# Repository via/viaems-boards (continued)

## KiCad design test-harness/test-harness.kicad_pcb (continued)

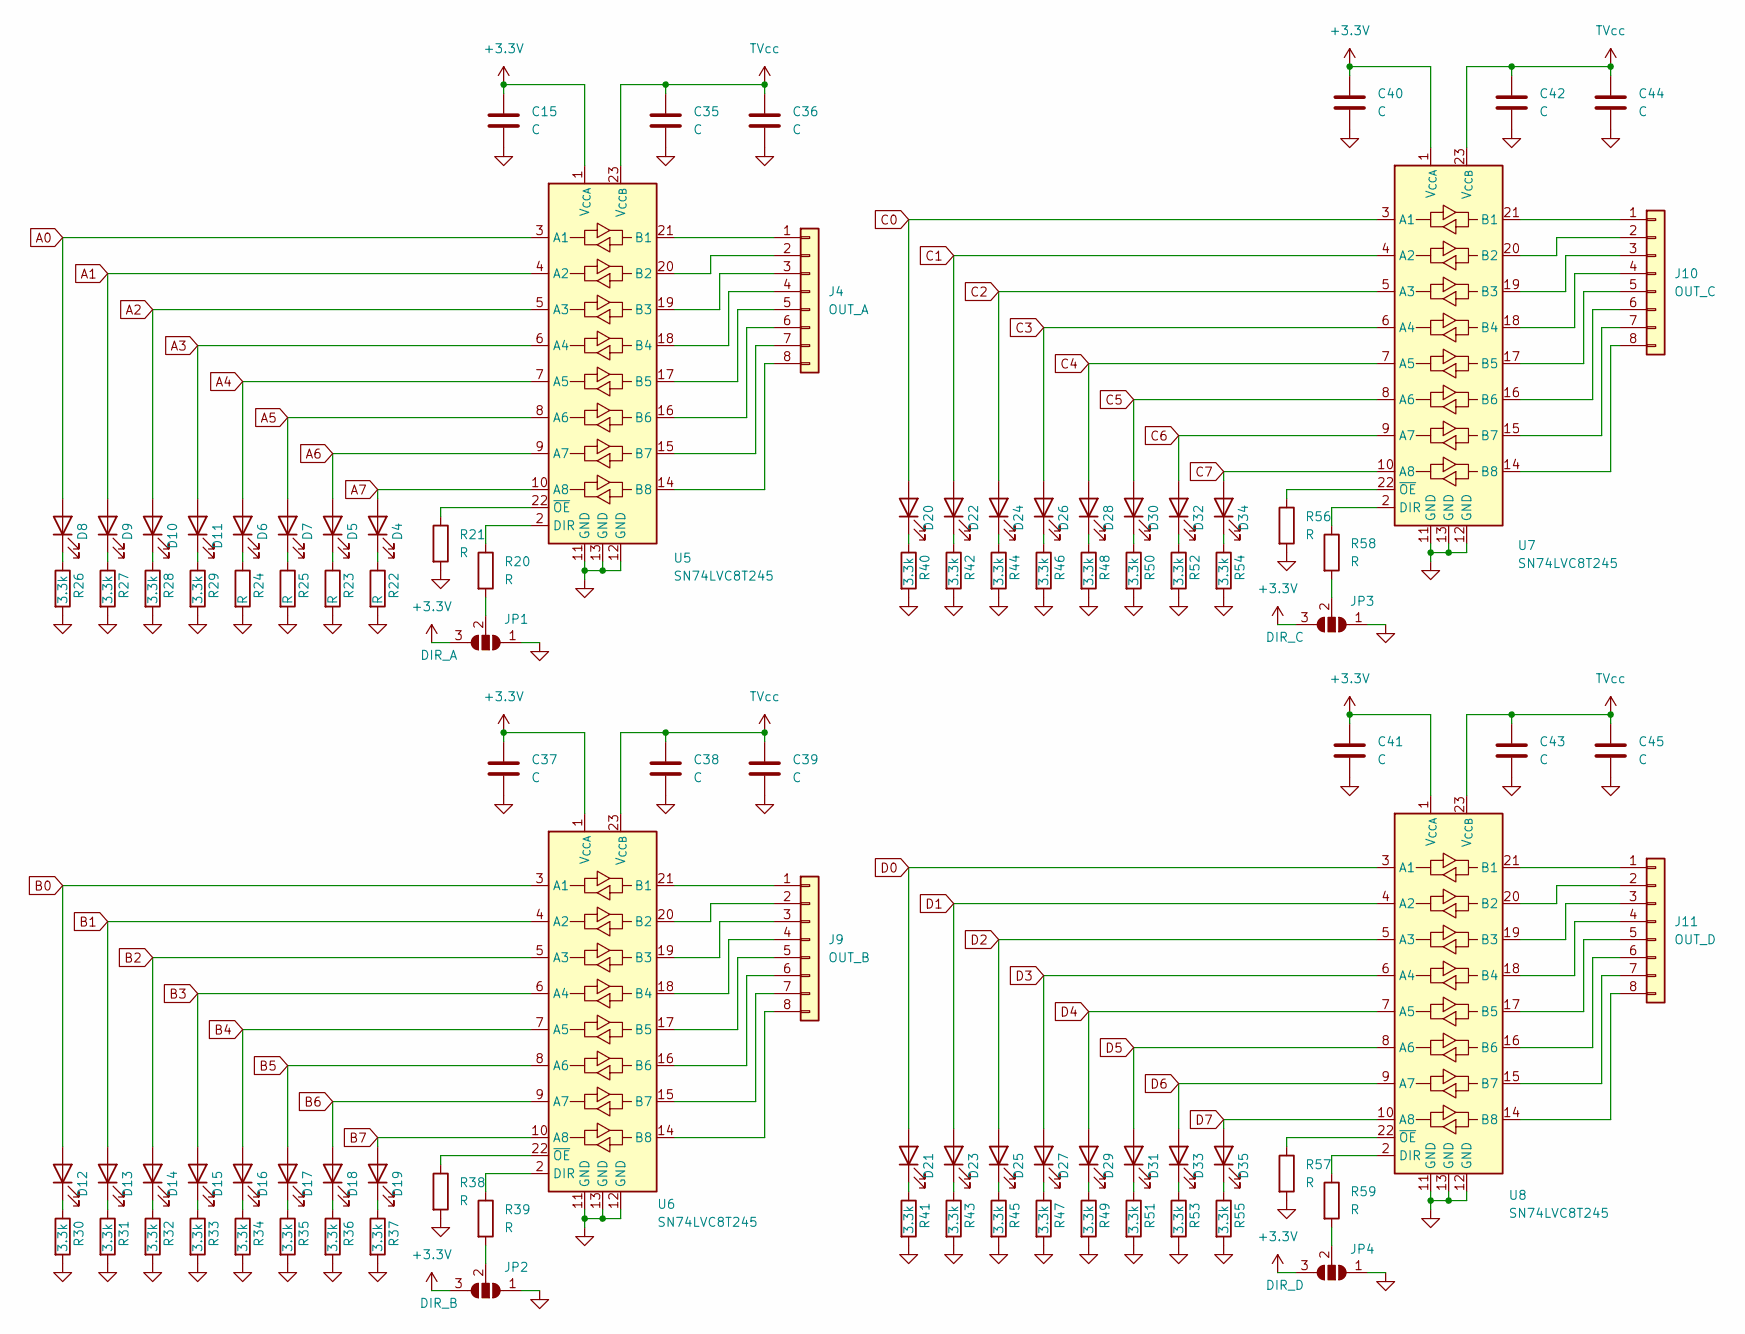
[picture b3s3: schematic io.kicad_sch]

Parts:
C15, C35, C36, C37, C38, C39, C40, C41, C42, C43, C44, C45: C; C_0805_2012Metric
D4, D5, D6, D7, D8, D9, D10, D11, D12, D13, D14, D15, D16, D17, D18, D19, D20, D21, D22, D23, D24, D25, D26, D27, D28, D29, D30, D31, D32, D33, D34, D35: LED; LED_0805_2012Metric
J4: OUT_A; PinHeader_1x08_P2.54mm_Vertical
J9: OUT_B; PinHeader_1x08_P2.54mm_Vertical
J10: OUT_C; PinHeader_1x08_P2.54mm_Vertical
J11: OUT_D; PinHeader_1x08_P2.54mm_Vertical
JP1: DIR_A; SolderJumper-3_P2.0mm_Open_TrianglePad1.0x1.5mm
JP2: DIR_B; SolderJumper-3_P2.0mm_Open_TrianglePad1.0x1.5mm
JP3: DIR_C; SolderJumper-3_P2.0mm_Open_TrianglePad1.0x1.5mm
JP4: DIR_D; SolderJumper-3_P2.0mm_Open_TrianglePad1.0x1.5mm
R20, R21, R22, R23, R24, R25, R38, R39, R56, R57, R58, R59: R; R_0805_2012Metric
R26, R27, R28, R29, R30, R31, R32, R33, R34, R35, R36, R37, R40, R41, R42, R43, R44, R45, R46, R47, R48, R49, R50, R51, R52, R53, R54, R55: 3.3k; R_0805_2012Metric
U5, U6, U7, U8: SN74LVC8T245; TSSOP-24_4.4x7.8mm_P0.65mm

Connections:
+3.3V: C15.1, C37.1, C40.1, C41.1, JP1.3 (B), JP2.3 (B), JP3.3 (B), JP4.3 (B), U5.1 (V_{CCA}), U6.1 (V_{CCA}), U7.1 (V_{CCA}), U8.1 (V_{CCA}); also elsewhere on the board
A0: D8.2 (A), U5.3 (A1); also elsewhere on the board
A1: D9.2 (A), U5.4 (A2); also elsewhere on the board
A2: D10.2 (A), U5.5 (A3); also elsewhere on the board
A3: D11.2 (A), U5.6 (A4); also elsewhere on the board
A4: D6.2 (A), U5.7 (A5); also elsewhere on the board
A5: D7.2 (A), U5.8 (A6); also elsewhere on the board
A6: D5.2 (A), U5.9 (A7); also elsewhere on the board
A7: D4.2 (A), U5.10 (A8); also elsewhere on the board
B0: D12.2 (A), U6.3 (A1); also elsewhere on the board
B1: D13.2 (A), U6.4 (A2); also elsewhere on the board
B2: D14.2 (A), U6.5 (A3); also elsewhere on the board
B3: D15.2 (A), U6.6 (A4); also elsewhere on the board
B4: D16.2 (A), U6.7 (A5); also elsewhere on the board
B5: D17.2 (A), U6.8 (A6); also elsewhere on the board
B6: D18.2 (A), U6.9 (A7); also elsewhere on the board
B7: D19.2 (A), U6.10 (A8); also elsewhere on the board
C0: D20.2 (A), U7.3 (A1); also elsewhere on the board
C1: D22.2 (A), U7.4 (A2); also elsewhere on the board
C2: D24.2 (A), U7.5 (A3); also elsewhere on the board
C3: D26.2 (A), U7.6 (A4); also elsewhere on the board
C4: D28.2 (A), U7.7 (A5); also elsewhere on the board
C5: D30.2 (A), U7.8 (A6); also elsewhere on the board
C6: D32.2 (A), U7.9 (A7); also elsewhere on the board
C7: D34.2 (A), U7.10 (A8); also elsewhere on the board
D0: D21.2 (A), U8.3 (A1); also elsewhere on the board
D1: D23.2 (A), U8.4 (A2); also elsewhere on the board
D2: D25.2 (A), U8.5 (A3); also elsewhere on the board
D3: D27.2 (A), U8.6 (A4); also elsewhere on the board
D4: D29.2 (A), U8.7 (A5); also elsewhere on the board
D5: D31.2 (A), U8.8 (A6); also elsewhere on the board
D6: D33.2 (A), U8.9 (A7); also elsewhere on the board
D7: D35.2 (A), U8.10 (A8); also elsewhere on the board
GND: C15.2, C35.2, C36.2, C37.2, C38.2, C39.2, C40.2, C41.2, C42.2, C43.2, C44.2, C45.2, JP1.1 (A), JP2.1 (A), JP3.1 (A), JP4.1 (A), R21.2, R22.2, R23.2, R24.2, R25.2, R26.2, R27.2, R28.2, R29.2, R30.2, R31.2, R32.2, R33.2, R34.2, R35.2, R36.2, R37.2, R38.2, R40.2, R41.2, R42.2, R43.2, R44.2, R45.2, R46.2, R47.2, R48.2, R49.2, R50.2, R51.2, R52.2, R53.2, R54.2, R55.2, R56.2, R57.2, U5.11 (GND), U5.12 (GND), U5.13 (GND), U6.11 (GND), U6.12 (GND), U6.13 (GND), U7.11 (GND), U7.12 (GND), U7.13 (GND), U8.11 (GND), U8.12 (GND), U8.13 (GND); also elsewhere on the board
unnamed: D4.1 (K), R22.1
unnamed: D5.1 (K), R23.1
unnamed: D6.1 (K), R24.1
unnamed: D7.1 (K), R25.1
unnamed: D8.1 (K), R26.1
unnamed: D9.1 (K), R27.1
unnamed: D10.1 (K), R28.1
unnamed: D11.1 (K), R29.1
unnamed: D12.1 (K), R30.1
unnamed: D13.1 (K), R31.1
unnamed: D14.1 (K), R32.1
unnamed: D15.1 (K), R33.1
unnamed: D16.1 (K), R34.1
unnamed: D17.1 (K), R35.1
unnamed: D18.1 (K), R36.1
unnamed: D19.1 (K), R37.1
unnamed: D20.1 (K), R40.1
unnamed: D21.1 (K), R41.1
unnamed: D22.1 (K), R42.1
unnamed: D23.1 (K), R43.1
unnamed: D24.1 (K), R44.1
unnamed: D25.1 (K), R45.1
unnamed: D26.1 (K), R46.1
unnamed: D27.1 (K), R47.1
unnamed: D28.1 (K), R48.1
unnamed: D29.1 (K), R49.1
unnamed: D30.1 (K), R50.1
unnamed: D31.1 (K), R51.1
unnamed: D32.1 (K), R52.1
unnamed: D33.1 (K), R53.1
unnamed: D34.1 (K), R54.1
unnamed: D35.1 (K), R55.1
unnamed: J4.1, U5.21 (B1)
unnamed: J4.2, U5.20 (B2)
unnamed: J4.3, U5.19 (B3)
unnamed: J4.4, U5.18 (B4)
unnamed: J4.5, U5.17 (B5)
unnamed: J4.6, U5.16 (B6)
unnamed: J4.7, U5.15 (B7)
unnamed: J4.8, U5.14 (B8)
unnamed: J9.1, U6.21 (B1)
unnamed: J9.2, U6.20 (B2)
unnamed: J9.3, U6.19 (B3)
unnamed: J9.4, U6.18 (B4)
unnamed: J9.5, U6.17 (B5)
unnamed: J9.6, U6.16 (B6)
unnamed: J9.7, U6.15 (B7)
unnamed: J9.8, U6.14 (B8)
unnamed: J10.1, U7.21 (B1)
unnamed: J10.2, U7.20 (B2)
unnamed: J10.3, U7.19 (B3)
unnamed: J10.4, U7.18 (B4)
unnamed: J10.5, U7.17 (B5)
unnamed: J10.6, U7.16 (B6)
unnamed: J10.7, U7.15 (B7)
unnamed: J10.8, U7.14 (B8)
unnamed: J11.1, U8.21 (B1)
unnamed: J11.2, U8.20 (B2)
unnamed: J11.3, U8.19 (B3)
unnamed: J11.4, U8.18 (B4)
unnamed: J11.5, U8.17 (B5)
unnamed: J11.6, U8.16 (B6)
unnamed: J11.7, U8.15 (B7)
unnamed: J11.8, U8.14 (B8)
unnamed: JP1.2 (C), R20.2
unnamed: JP2.2 (C), R39.2
unnamed: JP3.2 (C), R58.2
unnamed: JP4.2 (C), R59.2
unnamed: R20.1, U5.2 (DIR)
unnamed: R21.1, U5.22 (~OE)
unnamed: R39.1, U6.2 (DIR)
unnamed: R38.1, U6.22 (~OE)
unnamed: R58.1, U7.2 (DIR)
unnamed: R56.1, U7.22 (~OE)
unnamed: R59.1, U8.2 (DIR)
unnamed: R57.1, U8.22 (~OE)
TVcc: C35.1, C36.1, C38.1, C39.1, C42.1, C43.1, C44.1, C45.1, U5.23 (V_{CCB}), U5.24 (V_{CCB}), U6.23 (V_{CCB}), U6.24 (V_{CCB}), U7.23 (V_{CCB}), U7.24 (V_{CCB}), U8.23 (V_{CCB}), U8.24 (V_{CCB}); also elsewhere on the board

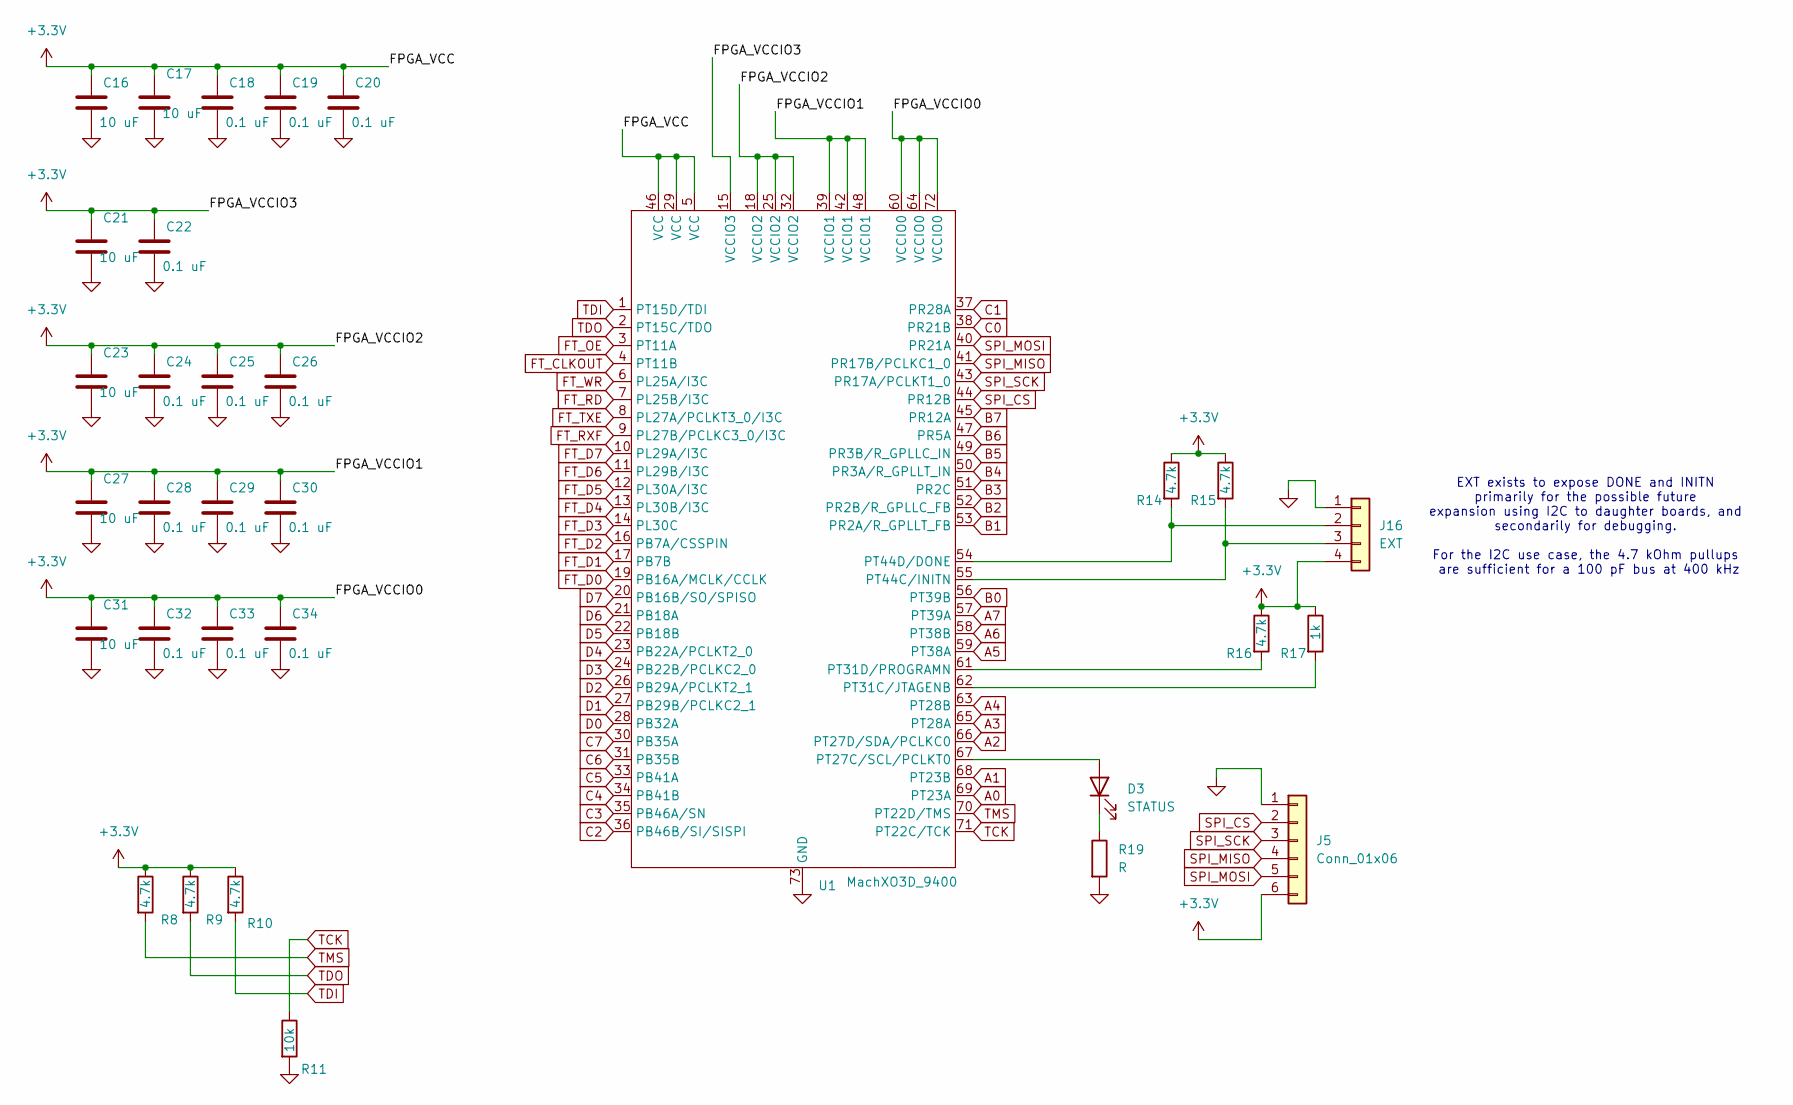
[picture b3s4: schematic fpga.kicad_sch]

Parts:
C16, C17, C21, C23, C27, C31: 10 uF; C_0805_2012Metric
C18, C19, C20, C22, C24, C25, C26, C28, C29, C30, C32, C33, C34: 0.1 uF; C_0805_2012Metric
D3: STATUS; LED_0805_2012Metric
J5: Conn_01x06; PinHeader_1x06_P2.54mm_Vertical
J16: EXT; PinHeader_1x04_P2.54mm_Vertical
R8, R9, R10, R14, R15, R16: 4.7k; R_0805_2012Metric
R11: 10k; R_0805_2012Metric
R17: 1k; R_0805_2012Metric
R19: R; R_0805_2012Metric
U1: MachXO3D_9400; QFN50P1000X1000X90-73N

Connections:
+3.3V: C16.1, C17.1, C18.1, C19.1, C20.1, C21.1, C22.1, C23.1, C24.1, C25.1, C26.1, C27.1, C28.1, C29.1, C30.1, C31.1, C32.1, C33.1, C34.1, J5.6, J16.4, R8.1, R9.1, R10.1, R14.1, R15.1, R16.1, R17.1, U1.5 (VCC), U1.15 (VCCIO3), U1.18 (VCCIO2), U1.25 (VCCIO2), U1.29 (VCC), U1.32 (VCCIO2), U1.39 (VCCIO1), U1.42 (VCCIO1), U1.46 (VCC), U1.48 (VCCIO1), U1.60 (VCCIO0), U1.64 (VCCIO0), U1.72 (VCCIO0); also elsewhere on the board
A0: U1.69 (PT23A); also elsewhere on the board
A1: U1.68 (PT23B); also elsewhere on the board
A2: U1.66 (PT27D/SDA/PCLKC0); also elsewhere on the board
A3: U1.65 (PT28A); also elsewhere on the board
A4: U1.63 (PT28B); also elsewhere on the board
A5: U1.59 (PT38A); also elsewhere on the board
A6: U1.58 (PT38B); also elsewhere on the board
A7: U1.57 (PT39A); also elsewhere on the board
B0: U1.56 (PT39B); also elsewhere on the board
B1: U1.53 (PR2A/R_GPLLT_FB); also elsewhere on the board
B2: U1.52 (PR2B/R_GPLLC_FB); also elsewhere on the board
B3: U1.51 (PR2C); also elsewhere on the board
B4: U1.50 (PR3A/R_GPLLT_IN); also elsewhere on the board
B5: U1.49 (PR3B/R_GPLLC_IN); also elsewhere on the board
B6: U1.47 (PR5A); also elsewhere on the board
B7: U1.45 (PR12A); also elsewhere on the board
C0: U1.38 (PR21B); also elsewhere on the board
C1: U1.37 (PR28A); also elsewhere on the board
C2: U1.36 (PB46B/SI/SISPI); also elsewhere on the board
C3: U1.35 (PB46A/SN); also elsewhere on the board
C4: U1.34 (PB41B); also elsewhere on the board
C5: U1.33 (PB41A); also elsewhere on the board
C6: U1.31 (PB35B); also elsewhere on the board
C7: U1.30 (PB35A); also elsewhere on the board
D0: U1.28 (PB32A); also elsewhere on the board
D1: U1.27 (PB29B/PCLKC2_1); also elsewhere on the board
D2: U1.26 (PB29A/PCLKT2_1); also elsewhere on the board
D3: U1.24 (PB22B/PCLKC2_0); also elsewhere on the board
D4: U1.23 (PB22A/PCLKT2_0); also elsewhere on the board
D5: U1.22 (PB18B); also elsewhere on the board
D6: U1.21 (PB18A); also elsewhere on the board
D7: U1.20 (PB16B/SO/SPISO); also elsewhere on the board
FT_CLKOUT: U1.4 (PT11B); also elsewhere on the board
FT_D0: U1.19 (PB16A/MCLK/CCLK); also elsewhere on the board
FT_D1: U1.17 (PB7B); also elsewhere on the board
FT_D2: U1.16 (PB7A/CSSPIN); also elsewhere on the board
FT_D3: U1.14 (PL30C); also elsewhere on the board
FT_D4: U1.13 (PL30B/I3C); also elsewhere on the board
FT_D5: U1.12 (PL30A/I3C); also elsewhere on the board
FT_D6: U1.11 (PL29B/I3C); also elsewhere on the board
FT_D7: U1.10 (PL29A/I3C); also elsewhere on the board
FT_OE: U1.3 (PT11A); also elsewhere on the board
FT_RD: U1.7 (PL25B/I3C); also elsewhere on the board
FT_RXF: U1.9 (PL27B/PCLKC3_0/I3C); also elsewhere on the board
FT_TXE: U1.8 (PL27A/PCLKT3_0/I3C); also elsewhere on the board
FT_WR: U1.6 (PL25A/I3C); also elsewhere on the board
GND: C16.2, C17.2, C18.2, C19.2, C20.2, C21.2, C22.2, C23.2, C24.2, C25.2, C26.2, C27.2, C28.2, C29.2, C30.2, C31.2, C32.2, C33.2, C34.2, J5.1, J16.1, R11.2, R19.2, U1.73 (GND); also elsewhere on the board
unnamed: D3.2 (A), U1.67 (PT27C/SCL/PCLKT0)
unnamed: D3.1 (K), R19.1
unnamed: J16.2, R14.2, U1.54 (PT44D/DONE)
unnamed: J16.3, R15.2, U1.55 (PT44C/INITN)
unnamed: R17.2, U1.62 (PT31C/JTAGENB)
unnamed: R16.2, U1.61 (PT31D/PROGRAMN)
SPI_CS: J5.2, U1.44 (PR12B); also elsewhere on the board
SPI_MISO: J5.4, U1.41 (PR17B/PCLKC1_0)
SPI_MOSI: J5.5, U1.40 (PR21A); also elsewhere on the board
SPI_SCK: J5.3, U1.43 (PR17A/PCLKT1_0); also elsewhere on the board
TCK: R11.1, U1.71 (PT22C/TCK); also elsewhere on the board
TDI: R10.2, U1.1 (PT15D/TDI); also elsewhere on the board
TDO: R9.2, U1.2 (PT15C/TDO); also elsewhere on the board
TMS: R8.2, U1.70 (PT22D/TMS); also elsewhere on the board

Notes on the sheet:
EXT exists to expose DONE and INITN primarily for the possible future expansion using I2C to daughter boards, and secondarily for debugging. For the I2C use case, the 4.7 kOhm pullups are sufficient for a 100 pF bus at 400 kHz

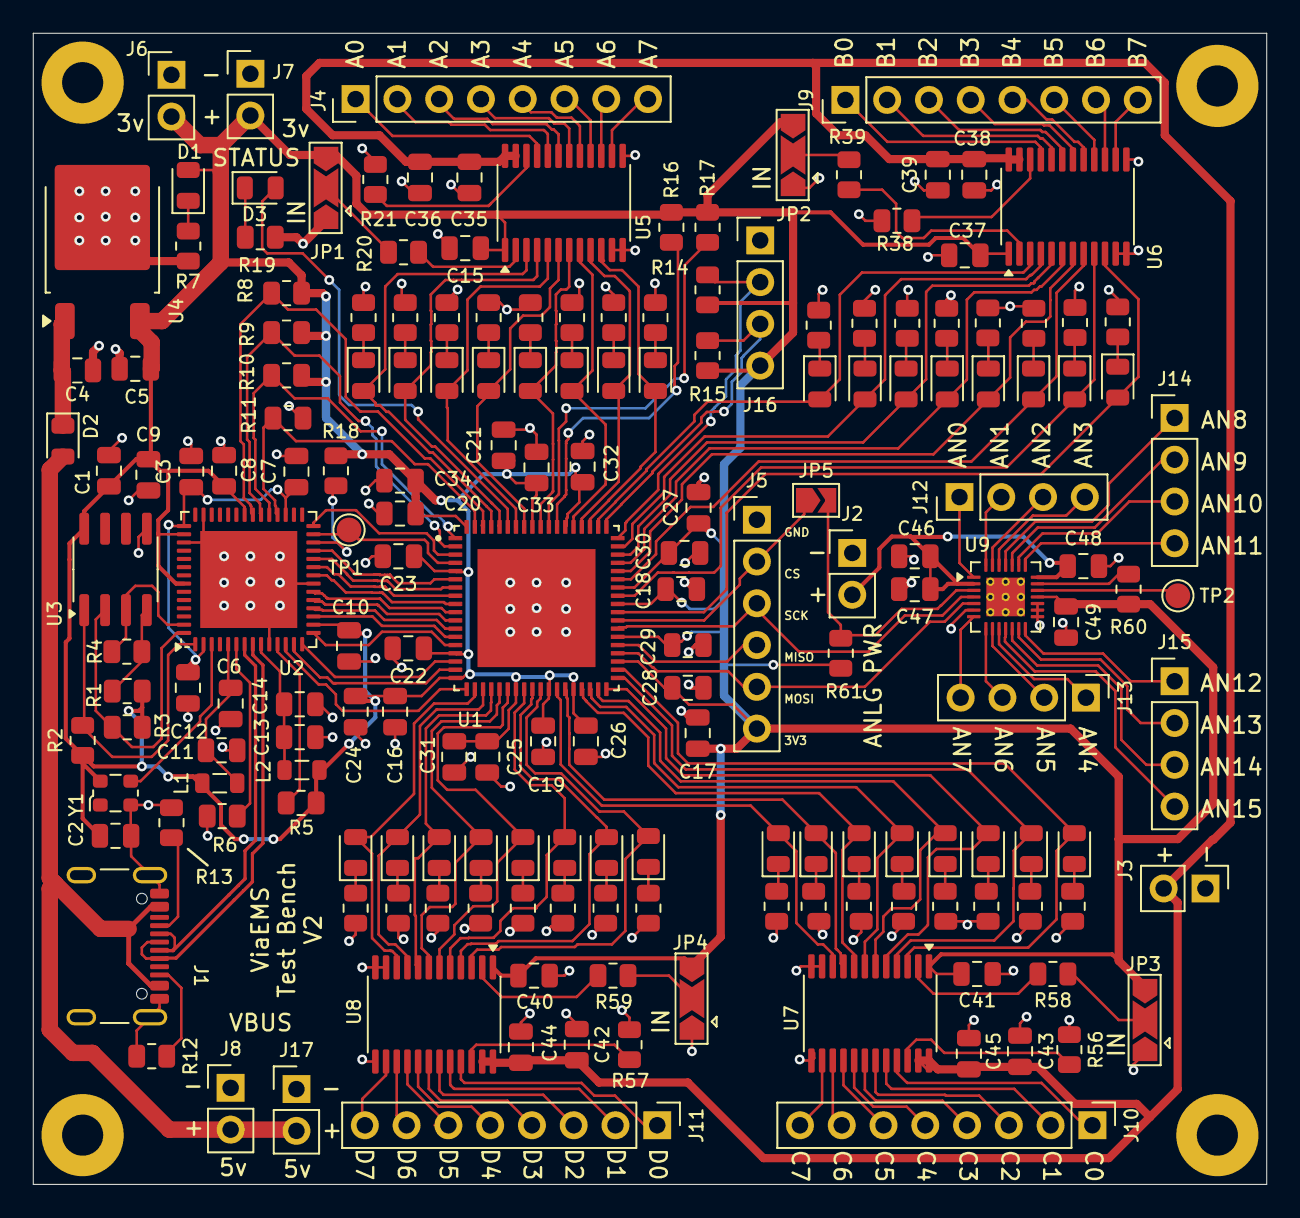
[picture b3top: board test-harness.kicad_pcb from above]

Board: 2 copper layers, 75.0 x 70.0 mm, 185 parts (0 on the bottom side), 177 nets.

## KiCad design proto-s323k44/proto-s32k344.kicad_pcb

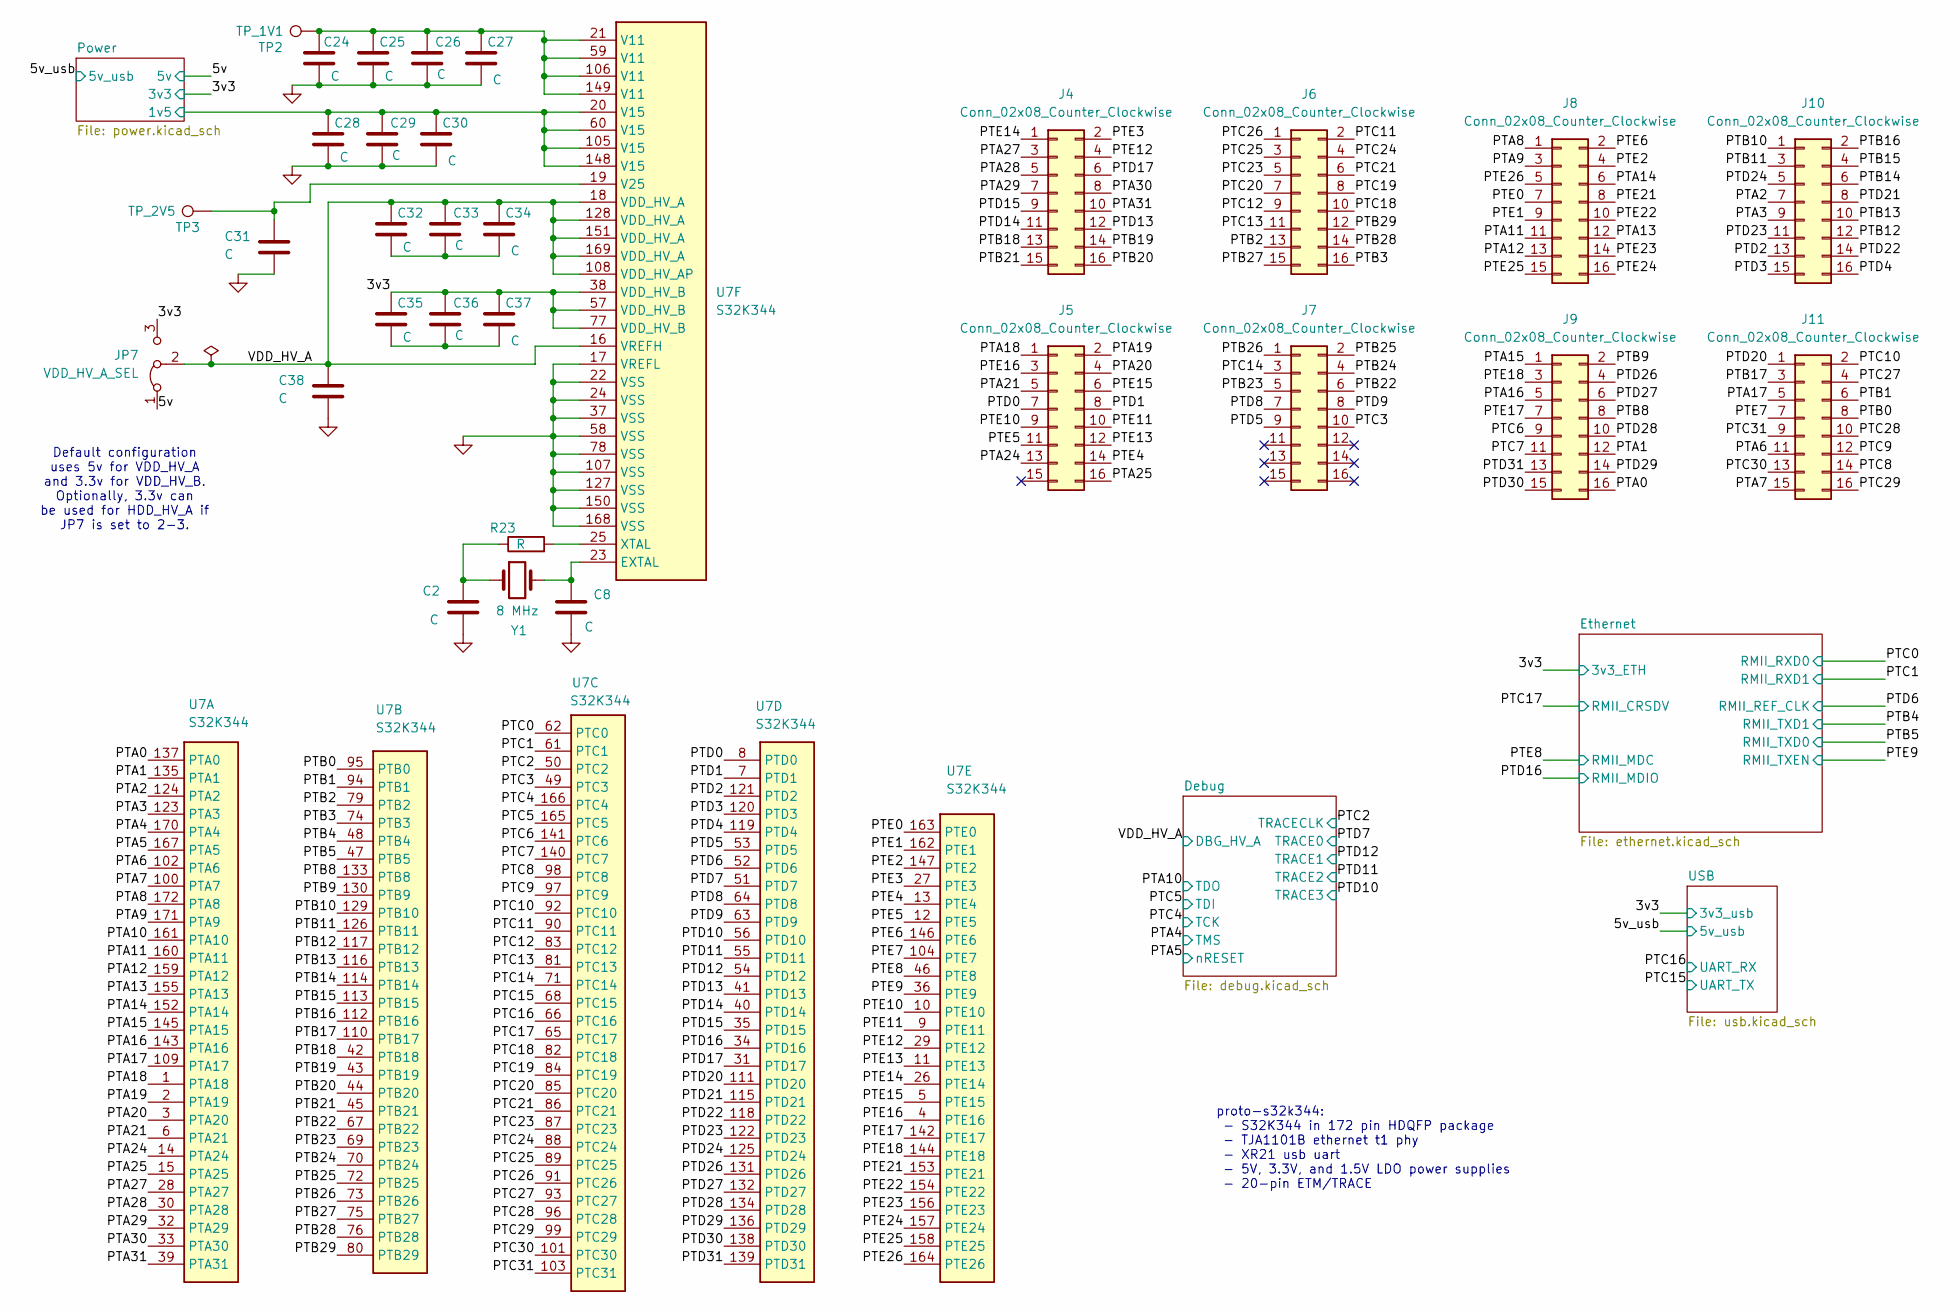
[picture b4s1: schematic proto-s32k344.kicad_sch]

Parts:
C2, C8, C24, C25, C26, C27, C28, C29, C30, C31, C32, C33, C34, C35, C36, C37, C38: C; C_0805_2012Metric
J4, J5, J6, J7, J8, J9, J10, J11: Conn_02x08_Counter_Clockwise; PinHeader_2x08_P2.54mm_Vertical
JP7: VDD_HV_A_SEL; PinHeader_1x03_P2.54mm_Vertical
R23: R; R_0805_2012Metric
TP2: TP_1V1; TestPoint_Pad_D1.5mm
TP3: TP_2V5; TestPoint_Pad_D1.5mm
U7: S32K344; IC_S32K344NHT1MPBST
Y1: 8 MHz; Crystal_HC49-U_Vertical; Digikey-part 535-10212-2-ND

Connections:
/3v3: C35.1, C36.1, C37.1, JP7.3 (B), U7.38 (VDD_HV_B), U7.57 (VDD_HV_B), U7.77 (VDD_HV_B); also elsewhere on the board
/5v: JP7.1 (A); also elsewhere on the board
/PTA0: J9.16, U7.137 (PTA0)
/PTA1: J9.12, U7.135 (PTA1)
/PTA2: J10.7, U7.124 (PTA2)
/PTA3: J10.9, U7.123 (PTA3)
/PTA4: U7.170 (PTA4); also elsewhere on the board
/PTA5: U7.167 (PTA5); also elsewhere on the board
/PTA6: J11.11, U7.102 (PTA6)
/PTA7: J11.15, U7.100 (PTA7)
/PTA8: J8.1, U7.172 (PTA8)
/PTA9: J8.3, U7.171 (PTA9)
/PTA10: U7.161 (PTA10); also elsewhere on the board
/PTA11: J8.11, U7.160 (PTA11)
/PTA12: J8.13, U7.159 (PTA12)
/PTA13: J8.12, U7.155 (PTA13)
/PTA14: J8.6, U7.152 (PTA14)
/PTA15: J9.1, U7.145 (PTA15)
/PTA16: J9.5, U7.143 (PTA16)
/PTA17: J11.5, U7.109 (PTA17)
/PTA18: J5.1, U7.1 (PTA18)
/PTA19: J5.2, U7.2 (PTA19)
/PTA20: J5.4, U7.3 (PTA20)
/PTA21: J5.5, U7.6 (PTA21)
/PTA24: J5.13, U7.14 (PTA24)
/PTA25: J5.16, U7.15 (PTA25)
/PTA27: J4.3, U7.28 (PTA27)
/PTA28: J4.5, U7.30 (PTA28)
/PTA29: J4.7, U7.32 (PTA29)
/PTA30: J4.8, U7.33 (PTA30)
/PTA31: J4.10, U7.39 (PTA31)
/PTB0: J11.8, U7.95 (PTB0)
/PTB1: J11.6, U7.94 (PTB1)
/PTB2: J6.13, U7.79 (PTB2)
/PTB3: J6.16, U7.74 (PTB3)
/PTB4: U7.48 (PTB4); also elsewhere on the board
/PTB5: U7.47 (PTB5); also elsewhere on the board
/PTB8: J9.8, U7.133 (PTB8)
/PTB9: J9.2, U7.130 (PTB9)
/PTB10: J10.1, U7.129 (PTB10)
/PTB11: J10.3, U7.126 (PTB11)
/PTB12: J10.12, U7.117 (PTB12)
/PTB13: J10.10, U7.116 (PTB13)
/PTB14: J10.6, U7.114 (PTB14)
/PTB15: J10.4, U7.113 (PTB15)
/PTB16: J10.2, U7.112 (PTB16)
/PTB17: J11.3, U7.110 (PTB17)
/PTB18: J4.13, U7.42 (PTB18)
/PTB19: J4.14, U7.43 (PTB19)
/PTB20: J4.16, U7.44 (PTB20)
/PTB21: J4.15, U7.45 (PTB21)
/PTB22: J7.6, U7.67 (PTB22)
/PTB23: J7.5, U7.69 (PTB23)
/PTB24: J7.4, U7.70 (PTB24)
/PTB25: J7.2, U7.72 (PTB25)
/PTB26: J7.1, U7.73 (PTB26)
/PTB27: J6.15, U7.75 (PTB27)
/PTB28: J6.14, U7.76 (PTB28)
/PTB29: J6.12, U7.80 (PTB29)
/PTC0: U7.62 (PTC0); also elsewhere on the board
/PTC1: U7.61 (PTC1); also elsewhere on the board
/PTC2: U7.50 (PTC2); also elsewhere on the board
/PTC3: J7.10, U7.49 (PTC3)
/PTC4: U7.166 (PTC4); also elsewhere on the board
/PTC5: U7.165 (PTC5); also elsewhere on the board
/PTC6: J9.9, U7.141 (PTC6)
/PTC7: J9.11, U7.140 (PTC7)
/PTC8: J11.14, U7.98 (PTC8)
/PTC9: J11.12, U7.97 (PTC9)
/PTC10: J11.2, U7.92 (PTC10)
/PTC11: J6.2, U7.90 (PTC11)
/PTC12: J6.9, U7.83 (PTC12)
/PTC13: J6.11, U7.81 (PTC13)
/PTC14: J7.3, U7.71 (PTC14)
/PTC15: U7.68 (PTC15); also elsewhere on the board
/PTC16: U7.66 (PTC16); also elsewhere on the board
/PTC17: U7.65 (PTC17); also elsewhere on the board
/PTC18: J6.10, U7.82 (PTC18)
/PTC19: J6.8, U7.84 (PTC19)
/PTC20: J6.7, U7.85 (PTC20)
/PTC21: J6.6, U7.86 (PTC21)
/PTC23: J6.5, U7.87 (PTC23)
/PTC24: J6.4, U7.88 (PTC24)
/PTC25: J6.3, U7.89 (PTC25)
/PTC26: J6.1, U7.91 (PTC26)
/PTC27: J11.4, U7.93 (PTC27)
/PTC28: J11.10, U7.96 (PTC28)
/PTC29: J11.16, U7.99 (PTC29)
/PTC30: J11.13, U7.101 (PTC30)
/PTC31: J11.9, U7.103 (PTC31)
/PTD0: J5.7, U7.8 (PTD0)
/PTD1: J5.8, U7.7 (PTD1)
/PTD2: J10.13, U7.121 (PTD2)
/PTD3: J10.15, U7.120 (PTD3)
/PTD4: J10.16, U7.119 (PTD4)
/PTD5: J7.9, U7.53 (PTD5)
/PTD6: U7.52 (PTD6); also elsewhere on the board
/PTD7: U7.51 (PTD7); also elsewhere on the board
/PTD8: J7.7, U7.64 (PTD8)
/PTD9: J7.8, U7.63 (PTD9)
/PTD10: U7.56 (PTD10); also elsewhere on the board
/PTD11: U7.55 (PTD11); also elsewhere on the board
/PTD12: U7.54 (PTD12); also elsewhere on the board
/PTD13: J4.12, U7.41 (PTD13)
/PTD14: J4.11, U7.40 (PTD14)
/PTD15: J4.9, U7.35 (PTD15)
/PTD16: U7.34 (PTD16); also elsewhere on the board
/PTD17: J4.6, U7.31 (PTD17)
/PTD20: J11.1, U7.111 (PTD20)
/PTD21: J10.8, U7.115 (PTD21)
/PTD22: J10.14, U7.118 (PTD22)
/PTD23: J10.11, U7.122 (PTD23)
/PTD24: J10.5, U7.125 (PTD24)
/PTD26: J9.4, U7.131 (PTD26)
/PTD27: J9.6, U7.132 (PTD27)
/PTD28: J9.10, U7.134 (PTD28)
/PTD29: J9.14, U7.136 (PTD29)
/PTD30: J9.15, U7.138 (PTD30)
/PTD31: J9.13, U7.139 (PTD31)
/PTE0: J8.7, U7.163 (PTE0)
/PTE1: J8.9, U7.162 (PTE1)
/PTE2: J8.4, U7.147 (PTE2)
/PTE3: J4.2, U7.27 (PTE3)
/PTE4: J5.14, U7.13 (PTE4)
/PTE5: J5.11, U7.12 (PTE5)
/PTE6: J8.2, U7.146 (PTE6)
/PTE7: J11.7, U7.104 (PTE7)
/PTE8: U7.46 (PTE8); also elsewhere on the board
/PTE9: U7.36 (PTE9); also elsewhere on the board
/PTE10: J5.9, U7.10 (PTE10)
/PTE11: J5.10, U7.9 (PTE11)
/PTE12: J4.4, U7.29 (PTE12)
/PTE13: J5.12, U7.11 (PTE13)
/PTE14: J4.1, U7.26 (PTE14)
/PTE15: J5.6, U7.5 (PTE15)
/PTE16: J5.3, U7.4 (PTE16)
/PTE17: J9.7, U7.142 (PTE17)
/PTE18: J9.3, U7.144 (PTE18)
/PTE21: J8.8, U7.153 (PTE21)
/PTE22: J8.10, U7.154 (PTE22)
/PTE23: J8.14, U7.156 (PTE23)
/PTE24: J8.16, U7.157 (PTE24)
/PTE25: J8.15, U7.158 (PTE25)
/PTE26: J8.5, U7.164 (PTE26)
/Power/1v5: C28.1, C29.1, C30.1, U7.20 (V15), U7.60 (V15), U7.105 (V15), U7.148 (V15); also elsewhere on the board
/VDD_HV_A: C32.1, C33.1, C34.1, C38.1, JP7.2 (C), U7.16 (VREFH), U7.18 (VDD_HV_A), U7.108 (VDD_HV_AP), U7.128 (VDD_HV_A), U7.151 (VDD_HV_A), U7.169 (VDD_HV_A); also elsewhere on the board
GND: C2.2, C8.2, C24.2, C25.2, C26.2, C27.2, C28.2, C29.2, C30.2, C31.2, C38.2, U7.17 (VREFL), U7.22 (VSS), U7.24 (VSS), U7.37 (VSS), U7.58 (VSS), U7.78 (VSS), U7.107 (VSS), U7.127 (VSS), U7.150 (VSS), U7.168 (VSS); also elsewhere on the board
unnamed: C2.1, R23.1, Y1.1
unnamed: C24.1, C25.1, C26.1, C27.1, TP2.1, U7.21 (V11), U7.59 (V11), U7.106 (V11), U7.149 (V11)
unnamed: C32.2, C33.2, C34.2
unnamed: C35.2, C36.2, C37.2
unnamed: C8.1, U7.23 (EXTAL), Y1.2
unnamed: C31.1, TP3.1, U7.19 (V25)
unnamed: R23.2, U7.25 (XTAL)

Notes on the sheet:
Default configuration uses 5v for VDD_HV_A and 3.3v for VDD_HV_B. Optionally, 3.3v can be used for HDD_HV_A if JP7 is set to 2-3.
proto-s32k344: - S32K344 in 172 pin HDQFP package - TJA1101B ethernet t1 phy - XR21 usb uart - 5V, 3.3V, and 1.5V LDO power supplies - 20-pin ETM/TRACE

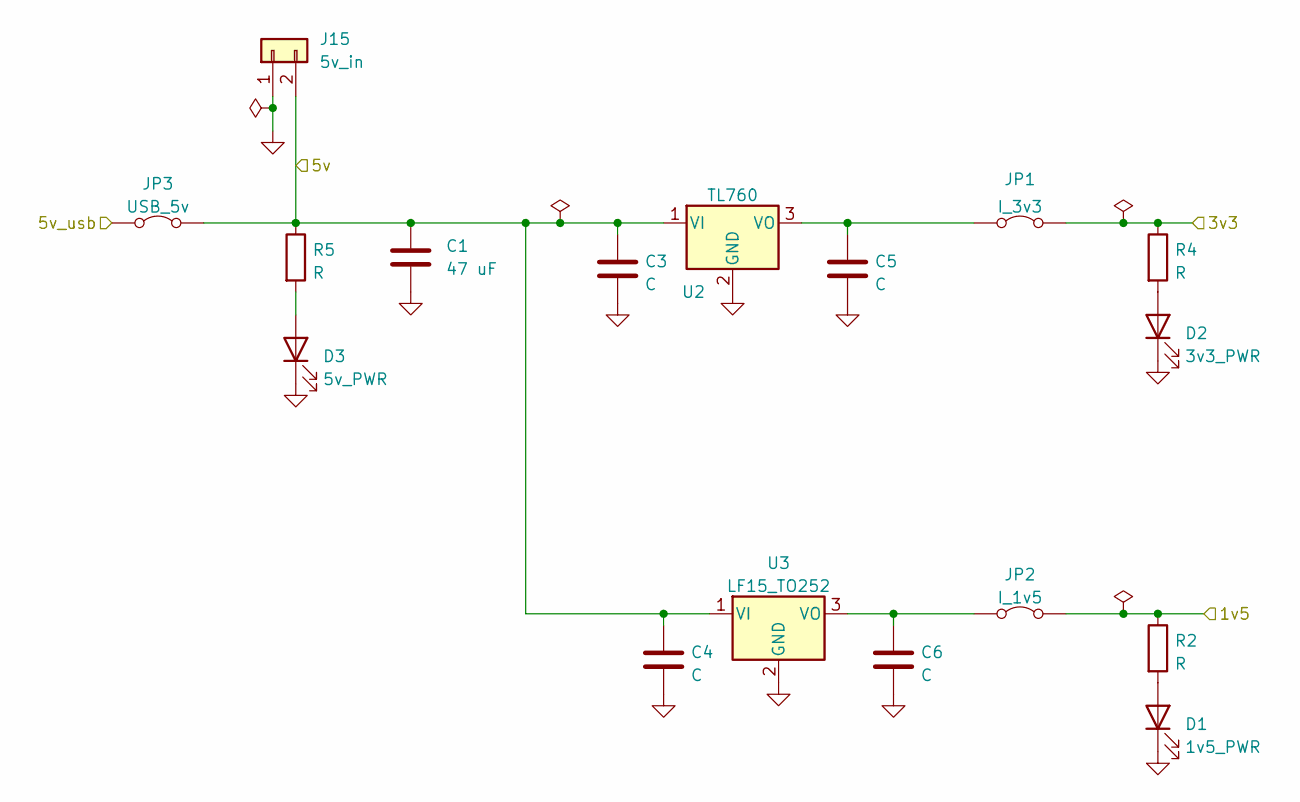
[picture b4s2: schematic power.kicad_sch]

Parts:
C1: 47 uF; C_0805_2012Metric
C3, C4, C5, C6: C; C_0805_2012Metric
D1: 1v5_PWR; D_0805_2012Metric
D2: 3v3_PWR; D_0805_2012Metric
D3: 5v_PWR; D_0805_2012Metric
J15: 5v_in; PinHeader_1x02_P2.54mm_Vertical
JP1: I_3v3; PinHeader_1x02_P2.54mm_Vertical
JP2: I_1v5; PinHeader_1x02_P2.54mm_Vertical
JP3: USB_5v; PinHeader_1x02_P2.54mm_Vertical
R2, R4, R5: R; R_0805_2012Metric
U2: TL760; TO-220-3_Vertical
U3: LF15_TO252; TO-252-2

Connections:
/3v3: JP1.2 (B), R4.1; also elsewhere on the board
/5v: C1.1, C3.1, C4.1, J15.2, JP3.2 (B), R5.1, U2.1 (VI), U3.1 (VI); also elsewhere on the board
/5v_usb: JP3.1 (A); also elsewhere on the board
/Power/1v5: JP2.2 (B), R2.1; also elsewhere on the board
GND: C1.2, C3.2, C4.2, C5.2, C6.2, D1.1 (K), D2.1 (K), D3.1 (K), J15.1, U2.2 (GND), U3.2 (GND); also elsewhere on the board
unnamed: D1.2 (A), R2.2
unnamed: D2.2 (A), R4.2
unnamed: D3.2 (A), R5.2
unnamed: C5.1, JP1.1 (A), U2.3 (VO)
unnamed: C6.1, JP2.1 (A), U3.3 (VO)
